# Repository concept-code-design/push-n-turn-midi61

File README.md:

# Push-n-Turn 61

Push-n-Turn 61 is a USB MIDI controller with 6 keyboard switches (RedDragon low profile), a rotary encoder and 7 RGB leds (WS8212).

The device sports a USB type-C connector and requires no device drivers on Mac or PC.

The keys can be configured (via MIDI messages, or the configurator) to produce notes, CC codes (momentary or toggle mode). The encoder produces 0..127 on a configurable CC channel. The encoder button produces 127/0 on a CC channel of choice.
Each switch has an RGB led that shows the state of the switch.
The device uses a modified midi library for CH55x devices made by mi:muz 

## Configuring the keys
Configuration of the keys can be done by sending midi codes to the device.
You can use python midiutil for this (https://github.com/sourcebox/midiutil).
The module listens to CC codes on channel 10 (0xBA on midiutil)

start configuration
0xBA, 0x64, 0x2A

end configuration and store data in EEprom
0xBA, 0x64, 0x2B

programming switches uses the following format
prefix (185) type+switch note/value
type is
	1: note mode
	2: CC momentary mode
	3: CC toggle mode
switch is 1..6
type and switch are combined into a number with first position for type, second for switch. So 12 is switch 2 in note mode, 35 is switch 5 in CC toggle mode
note/value is the note or CC code associated to the switch (C3 (middle C) is 60).

./midiutil.py -d 1 -w 185 11 60
will configure switch one to produce a C3 when pressed.

0xBA 0x64 0x2C
produces device type 0xBA 0x64 0x61 in [61, 31, 40, 51, F4] for 6key+1rot, you get the idea

0xBA 0x64 0x2D
returns the firmware revision: 0xBA, 0x64, 0x10 for instance for rev 1.0

## Links & References

* [mi:muz:ch55x Tiny USB MIDI Library for Ch55xduino](https://github.com/mimuz/mimuz-ch55x)
* 

# License

Concept & Code invests time and resources providing this open source design, please support them and open-source hardware by purchasing products from Etsy or Tindie!

Designed by Ronald Leenes.

Firmware released under an GNU AGPL v3.0 license. See the LICENSE file for more information.

Hardware released under an CERN Open Hardware Licence v1.2. See the LICENSE_HARDWARE file for more information.

February 2025

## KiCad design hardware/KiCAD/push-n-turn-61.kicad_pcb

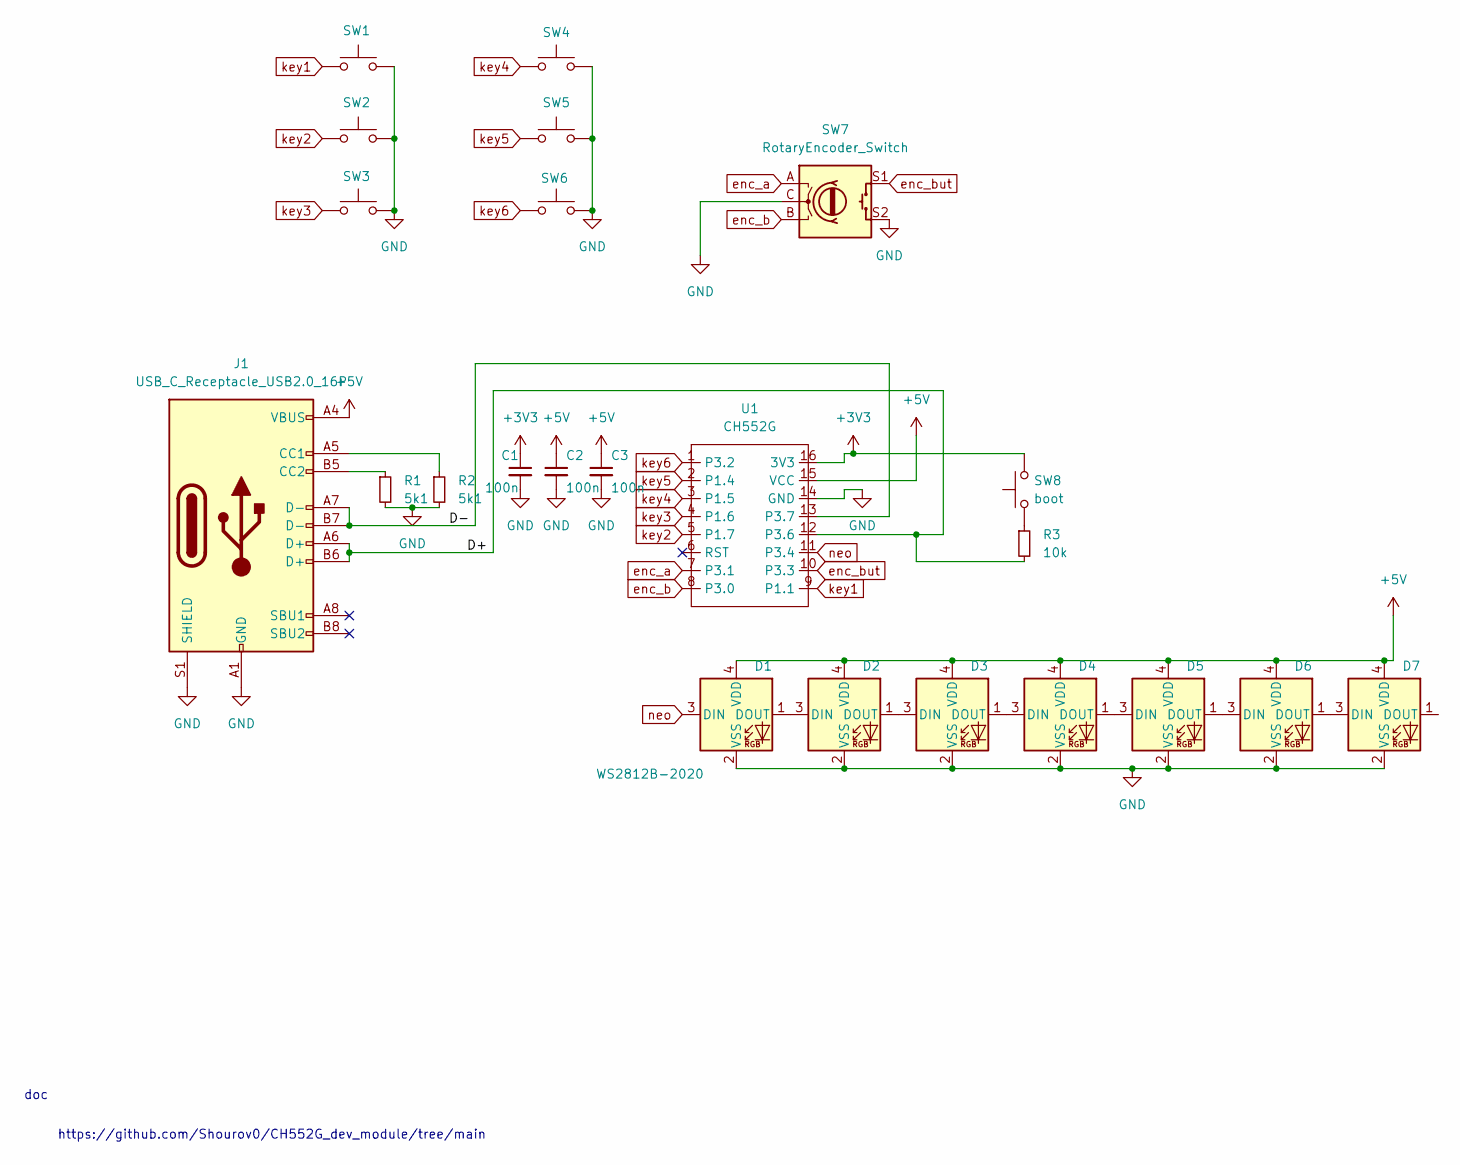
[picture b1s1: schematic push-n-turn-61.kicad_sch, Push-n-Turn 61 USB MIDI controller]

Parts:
C1, C2, C3: 100n; C_0805_2012Metric
D1, D2, D3, D4, D5, D6, D7: WS2812B-2020; LED_WS2812B-2020_PLCC4_2.0x2.0mm
J1: USB_C_Receptacle_USB2.0_16P; USB_C_Receptacle_GCT_USB4105-xx-A_16P_TopMnt_Horizontal
R1, R2: 5k1; R_0805_2012Metric
R3: 10k; R_0805_2012Metric
SW1: key1; SW_RedDragon5.5m_Ali_1.00u
SW2: key2; SW_RedDragon5.5m_Ali_1.00u
SW3, SW6: key3; SW_RedDragon5.5m_Ali_1.00u
SW4: key4; SW_RedDragon5.5m_Ali_1.00u
SW5: key5; SW_RedDragon5.5m_Ali_1.00u
SW7: RotaryEncoder_Switch; RotaryEncoder_Alps_EC11E_Vertical_H20mm
SW8: boot; SW_Push_SPST_NO_Alps_SKRK
U1: CH552G; SOP-16_4.4x10.4mm_P1.27mm

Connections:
+3V3: C1.1, SW8.2, U1.16 (3V3)
+5V: C2.1, C3.1, D1.4 (VDD), D2.4 (VDD), D3.4 (VDD), D4.4 (VDD), D5.4 (VDD), D6.4 (VDD), D7.4 (VDD), J1.A4 (VBUS), J1.A9 (VBUS), J1.B4 (VBUS), J1.B9 (VBUS), U1.15 (VCC)
/D+: J1.A6 (D+), J1.B6 (D+), R3.2, U1.12 (P3.6)
/D-: J1.A7 (D-), J1.B7 (D-), U1.13 (P3.7)
GND: C1.2, C2.2, C3.2, D1.2 (VSS), D2.2 (VSS), D3.2 (VSS), D4.2 (VSS), D5.2 (VSS), D6.2 (VSS), D7.2 (VSS), J1.A1 (GND), J1.A12 (GND), J1.B1 (GND), J1.B12 (GND), J1.S1 (SHIELD), R1.2, R2.2, SW1.2, SW2.2, SW3.2, SW4.2, SW5.2, SW6.2, SW7.C, SW7.S2, U1.14 (GND)
unnamed: D1.1 (DOUT), D2.3 (DIN)
unnamed: D2.1 (DOUT), D3.3 (DIN)
unnamed: D3.1 (DOUT), D4.3 (DIN)
unnamed: D4.1 (DOUT), D5.3 (DIN)
unnamed: D5.1 (DOUT), D6.3 (DIN)
unnamed: D6.1 (DOUT), D7.3 (DIN)
unnamed: J1.A5 (CC1), R2.1
unnamed: J1.B5 (CC2), R1.1
unnamed: R3.1, SW8.1
enc_a: SW7.A, U1.7 (P3.1)
enc_b: SW7.B, U1.8 (P3.0)
enc_but: SW7.S1, U1.10 (P3.3)
key1: SW1.1, U1.9 (P1.1)
key2: SW2.1, U1.5 (P1.7)
key3: SW3.1, U1.4 (P1.6)
key4: SW4.1, U1.3 (P1.5)
key5: SW5.1, U1.2 (P1.4)
key6: SW6.1, U1.1 (P3.2)
neo: D1.3 (DIN), U1.11 (P3.4)

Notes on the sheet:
https://github.com/Shourov0/CH552G_dev_module/tree/main
doc

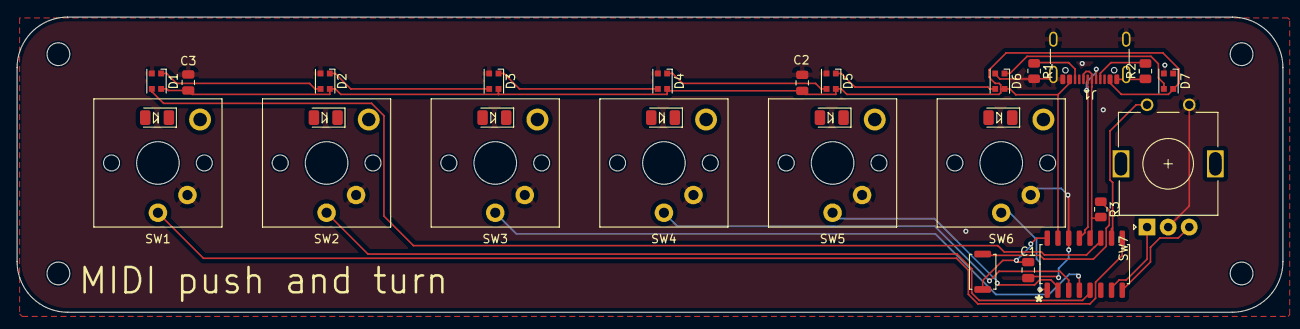
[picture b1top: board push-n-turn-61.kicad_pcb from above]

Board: 2 copper layers, 150.1 x 35.0 mm, 27 parts (0 on the bottom side), 24 nets.

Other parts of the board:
h1, h1#2, h1#3, h1#4: MountingHole_2.7mm_M2.5_ISO14580

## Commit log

2025-02-28 firmware v1.0
2025-03-23 small fixes
    small fixes
2025-04-26 compiled binaries
2025-05-14 added KiCad files
2026-02-12 Add test file for M5 stack Paper S3
2026-02-13 Convert message.txt to JSON format
